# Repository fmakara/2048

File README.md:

# 2048
2048 eletrônico. Leds RGB no lugar dos numeros que acendem seguindo a lógica do jogo.
4 botões de direção e mais botões de reiniciar jogo, salvar/resgatar, desfazer e refazer.

Compilado com Atmel Studio 6.1 e placa com KiCAD 2013

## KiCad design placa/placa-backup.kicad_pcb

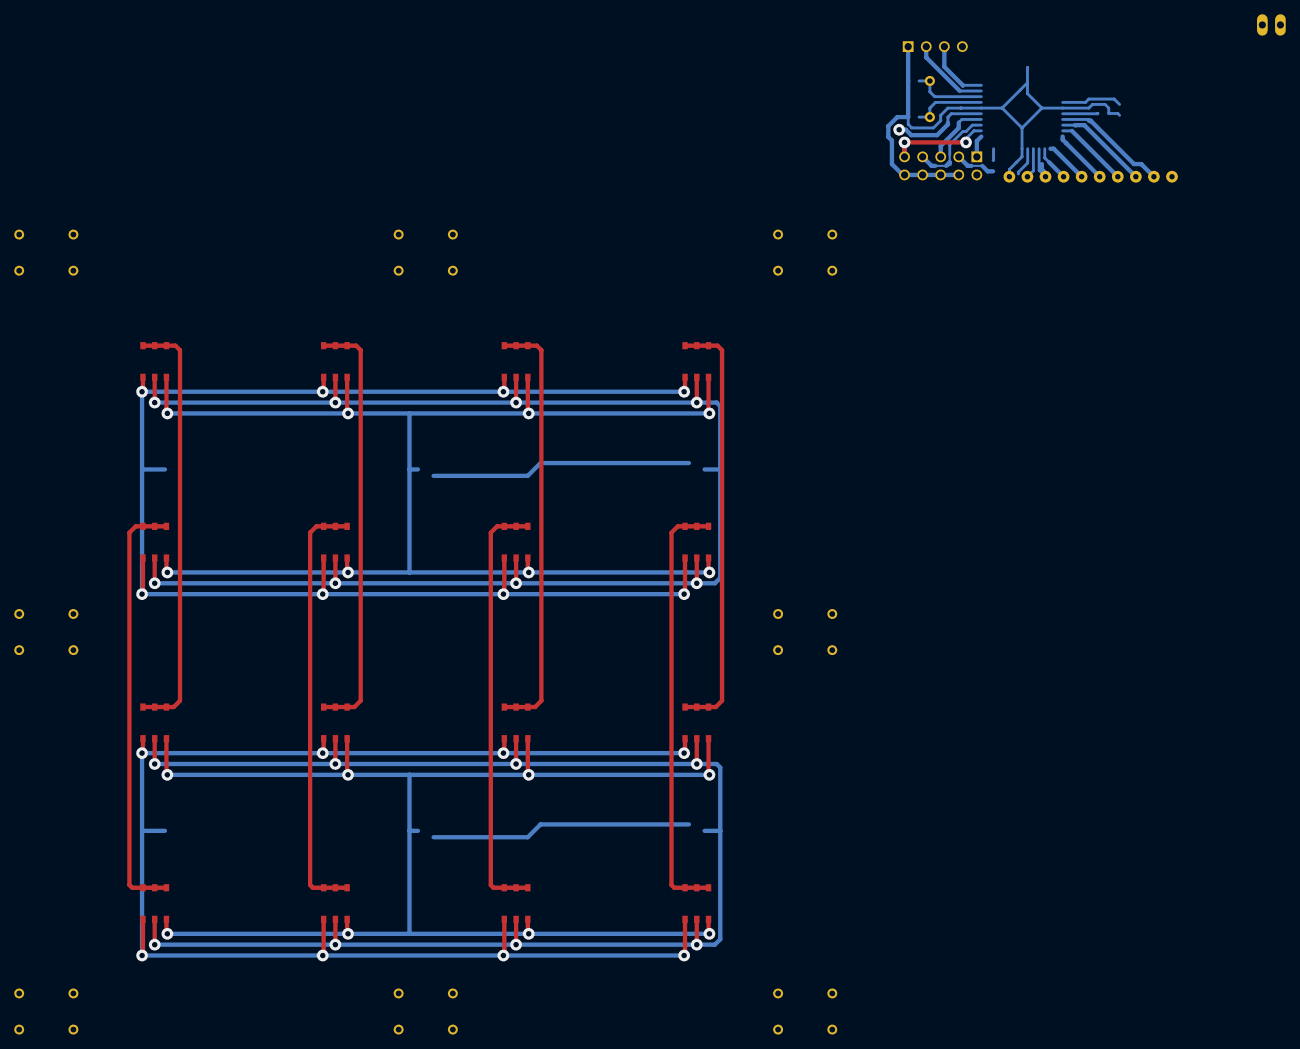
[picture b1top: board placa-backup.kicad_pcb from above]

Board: 2 copper layers, 44 parts (0 on the bottom side), 41 nets.

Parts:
C1, C2: 16p; SM0603
C3, C5, C6: 100n; SM0603
C4: 100u; SM1206POL
IC1: ATMEGA32-A; TQFP44
P1: ISP; PIN_ARRAY_5x2
P2: SERIAL; PIN_ARRAY_4x1
P3: INPUTS; CONN_10
P4: CONN_2; PINHEAD1-2
Q1, Q2, Q3, Q4, Q5, Q6: MOSFET_N; BSH103
R1: 0; SM0603
R2: 50k; SM0603
SW1, SW2, SW3, SW4, SW5, SW6, SW7, SW8: SW_PUSH; SW_PUSH_SMALL
U1, U2, U3, U4, U5, U6, U7, U8, U9, U10, U11, U12, U13, U14, U15, U16: LED3
X1: 16MHz; HC-49V

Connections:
+5V: C4.1, C5.1, C6.1, IC1.5, IC1.17, IC1.27, IC1.38, P1.2, P2.4, P3.10, P4.2, R2.2
/A_RESET: IC1.4, P1.5, R2.1
/L1: IC1.26, U2.1, U2.2, U2.3, U4.1, U4.2, U4.3
/L2: IC1.25, U6.1, U6.2, U6.3, U8.1, U8.2, U8.3
/L3: IC1.24, U10.1, U10.2, U10.3, U12.1, U12.2, U12.3
/L4: IC1.23, U14.1, U14.2, U14.3, U16.1, U16.2, U16.3
/L5: IC1.22, U1.1, U1.2, U1.3, U3.1, U3.2, U3.3
/L6: IC1.21, U5.1, U5.2, U5.3, U7.1, U7.2, U7.3
/L7: IC1.20, U9.1, U9.2, U9.3, U11.1, U11.2, U11.3
/L8: IC1.19, U13.1, U13.2, U13.3, U15.1, U15.2, U15.3
/SPI_CLK: IC1.3, P1.7
/SPI_MISO: IC1.2, P1.9
/SPI_MOSI: IC1.1, P1.1
/SPI_SS: IC1.44, R1.2
/T1: IC1.16, Q2.G
/T2: IC1.15, Q4.G
/T3: IC1.14, Q6.G
/T4: IC1.13, Q1.G
/T5: IC1.12, Q3.G
/T6: IC1.11, Q5.G
GND: C1.2, C2.2, C3.2, C4.2, C5.2, C6.2, IC1.6, IC1.18, IC1.28, IC1.39, P1.4, P1.6, P1.8, P1.10, P2.1, P3.1, P4.1, Q1.S, Q2.S, Q3.S, Q4.S, Q5.S, Q6.S, SW1.2, SW2.2, SW3.2, SW4.2, SW5.2, SW6.2, SW7.2, SW8.2
unnamed: Q1.D, U1.4, U2.4, U5.4, U6.4, U9.4, U10.4, U13.4, U14.4
unnamed: Q5.D, U1.6, U2.6, U5.6, U6.6, U9.6, U10.6, U13.6, U14.6
unnamed: Q3.D, U1.5, U2.5, U5.5, U6.5, U9.5, U10.5, U13.5, U14.5
unnamed: P1.3, R1.1
unnamed: Q2.D, U3.4, U4.4, U7.4, U8.4, U11.4, U12.4, U15.4, U16.4
unnamed: Q4.D, U3.5, U4.5, U7.5, U8.5, U11.5, U12.5, U15.5, U16.5
unnamed: IC1.10, P2.3
unnamed: IC1.37, P3.2, SW1.1
unnamed: IC1.36, P3.3, SW2.1
unnamed: IC1.35, P3.4, SW3.1
unnamed: IC1.34, P3.5, SW4.1
unnamed: IC1.33, P3.6, SW5.1
unnamed: IC1.32, P3.7, SW6.1
unnamed: IC1.31, P3.8, SW7.1
unnamed: IC1.30, P3.9, SW8.1
unnamed: IC1.9, P2.2
unnamed: C3.1, IC1.29
unnamed: C1.1, IC1.7, X1.2
unnamed: C2.1, IC1.8, X1.1
unnamed: Q6.D, U3.6, U4.6, U7.6, U8.6, U11.6, U12.6, U15.6, U16.6
